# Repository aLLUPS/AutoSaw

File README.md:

# AutoSaw

This repository contains the information about ATMEGA 32A micro-controller based project - The Automated Abrasive Saw - 'AutoSaw'.
* It is a machine which cuts long metal box bars into smaller pieces automatically, after the user enter the input length and number of pieces required.
* This repository consists:
    1. 3dModel:- The 3d model of the machine. (.FCSTD file & .stl file)
    2. Animation:- The animation about the operation of the machine.
    3. AtmelProject:- micro-C codes to program the whole machine.
    4. PCB:- The Printed circuit board design, the wiring of Electronic/Electric components with PCB.

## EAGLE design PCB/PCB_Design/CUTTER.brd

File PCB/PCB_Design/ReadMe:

* This folder contains the eagle project and images of the pcb design
* You can open the .sch and .brd files using Audodesk EAGLE software.

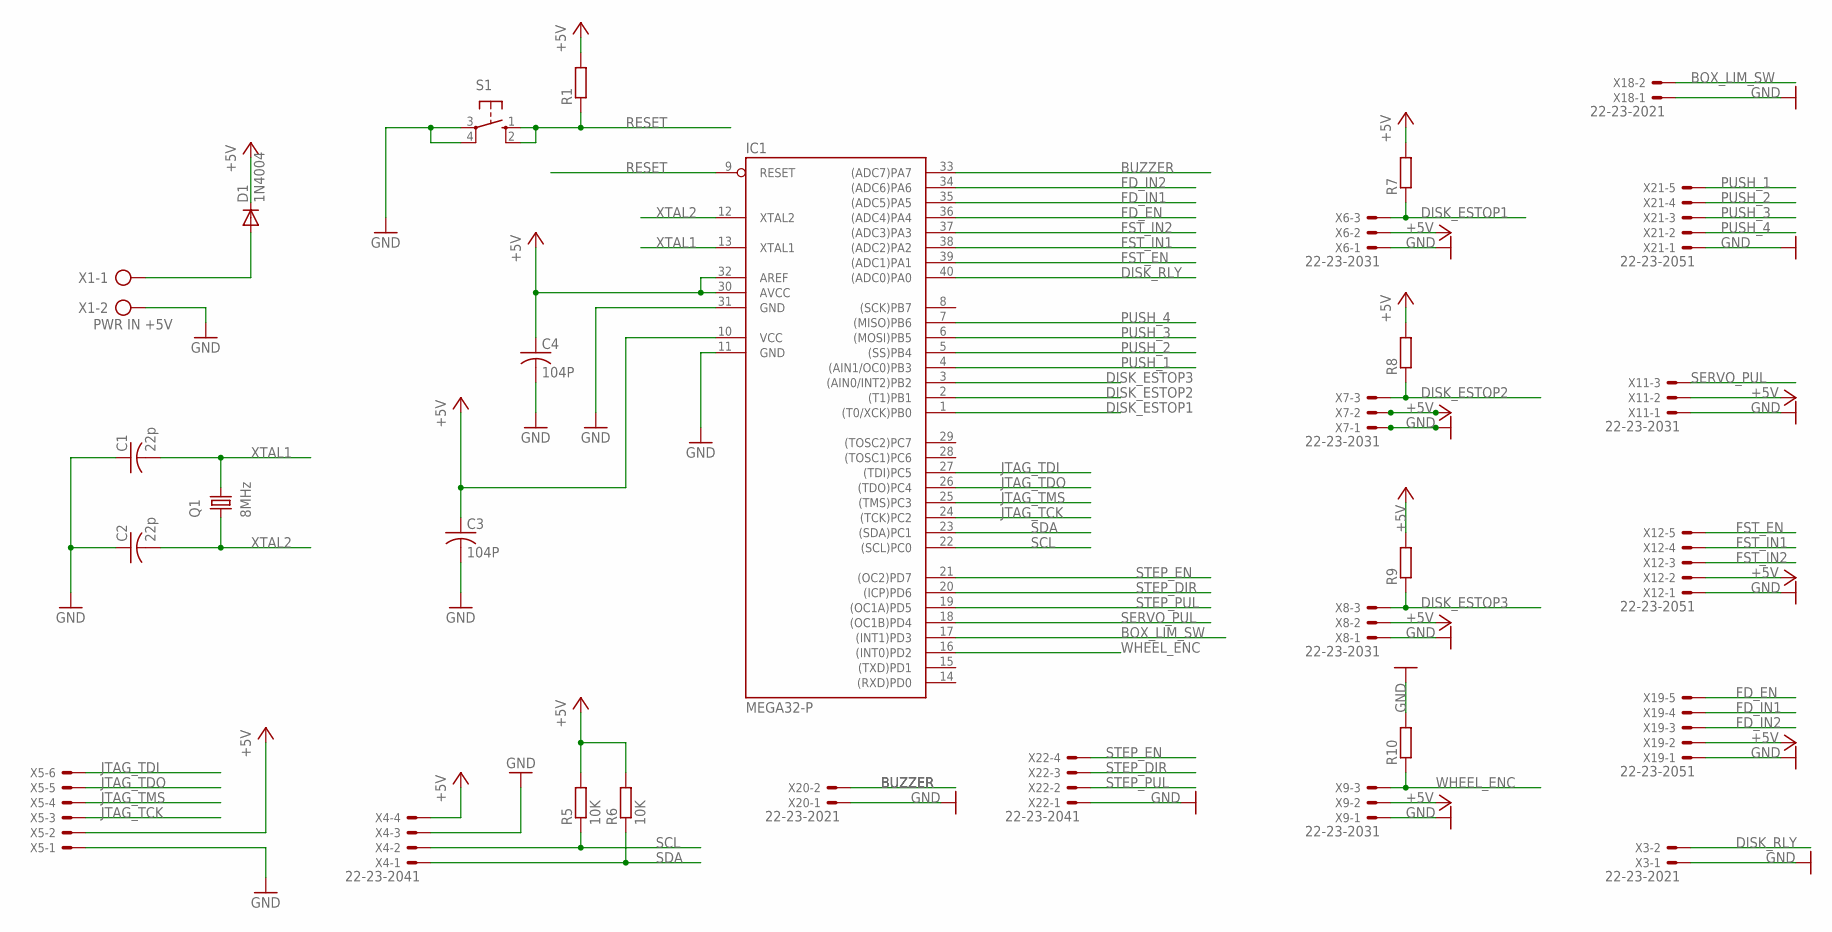
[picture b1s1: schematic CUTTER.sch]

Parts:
C1, C2: 22p; C025-025X050
C3, C4: 104P; C025-025X050
D1: 1N4004; DO41-10
IC1: MEGA32-P; DIL40
Q1: 8MHz; HC49/S
R1, R7, R8, R9, R10: R-EU_0207/10; 0207/10
R5, R6: 10K; 0207/10
S1: 10-XX; B3F-10XX
X1: PWR IN +5V; AK500/2
X3, X18, X20: 22-23-2021
X4, X22: 22-23-2041
X5: 22-23-2061
X6, X7, X8, X9, X11: 22-23-2031
X12, X19, X21: 22-23-2051

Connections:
+5V: C3.1, C4.1, D1.C, IC1.10 (VCC), IC1.30 (AVCC), IC1.32 (AREF), R1.2, R5.2, R6.2, R7.2, R8.2, R9.2, X4.4, X5.2, X6.2, X7.2, X8.2, X9.2, X11.2, X12.2, X19.2
BOX_LIM_SW: IC1.17 ((INT1)PD3), X18.2
BUZZER: IC1.33 ((ADC7)PA7), X20.2
DISK_ESTOP1: IC1.1 ((T0/XCK)PB0), R7.1, X6.3
DISK_ESTOP2: IC1.2 ((T1)PB1), R8.1, X7.3
DISK_ESTOP3: IC1.3 ((AIN0/INT2)PB2), R9.1, X8.3
DISK_RLY: IC1.40 ((ADC0)PA0), X3.2
FD_EN: IC1.36 ((ADC4)PA4), X19.5
FD_IN1: IC1.35 ((ADC5)PA5), X19.4
FD_IN2: IC1.34 ((ADC6)PA6), X19.3
FST_EN: IC1.39 ((ADC1)PA1), X12.5
FST_IN1: IC1.38 ((ADC2)PA2), X12.4
FST_IN2: IC1.37 ((ADC3)PA3), X12.3
GND: C1.1, C2.1, C3.2, C4.2, IC1.11 (GND), IC1.31 (GND), R10.2, S1.3, S1.4 (P1), X1.2, X3.1, X4.3, X5.1, X6.1, X7.1, X8.1, X9.1, X11.1, X12.1, X18.1, X19.1, X20.1, X21.1, X22.1
JTAG_TCK: IC1.24 ((TCK)PC2), X5.3
JTAG_TDI: IC1.27 ((TDI)PC5), X5.6
JTAG_TDO: IC1.26 ((TDO)PC4), X5.5
JTAG_TMS: IC1.25 ((TMS)PC3), X5.4
unnamed: D1.A, X1.1
PUSH_1: IC1.4 ((AIN1/OC0)PB3), X21.5
PUSH_2: IC1.5 ((SS)PB4), X21.4
PUSH_3: IC1.6 ((MOSI)PB5), X21.3
PUSH_4: IC1.7 ((MISO)PB6), X21.2
RESET: IC1.9 (RESET), R1.1, S1.1 (S), S1.2 (S1)
SCL: IC1.22 ((SCL)PC0), R5.1, X4.2
SDA: IC1.23 ((SDA)PC1), R6.1, X4.1
SERVO_PUL: IC1.18 ((OC1B)PD4), X11.3
STEP_DIR: IC1.20 ((ICP)PD6), X22.3
STEP_EN: IC1.21 ((OC2)PD7), X22.4
STEP_PUL: IC1.19 ((OC1A)PD5), X22.2
WHEEL_ENC: IC1.16 ((INT0)PD2), R10.1, X9.3
XTAL1: C1.2, IC1.13 (XTAL1), Q1.2
XTAL2: C2.2, IC1.12 (XTAL2), Q1.1

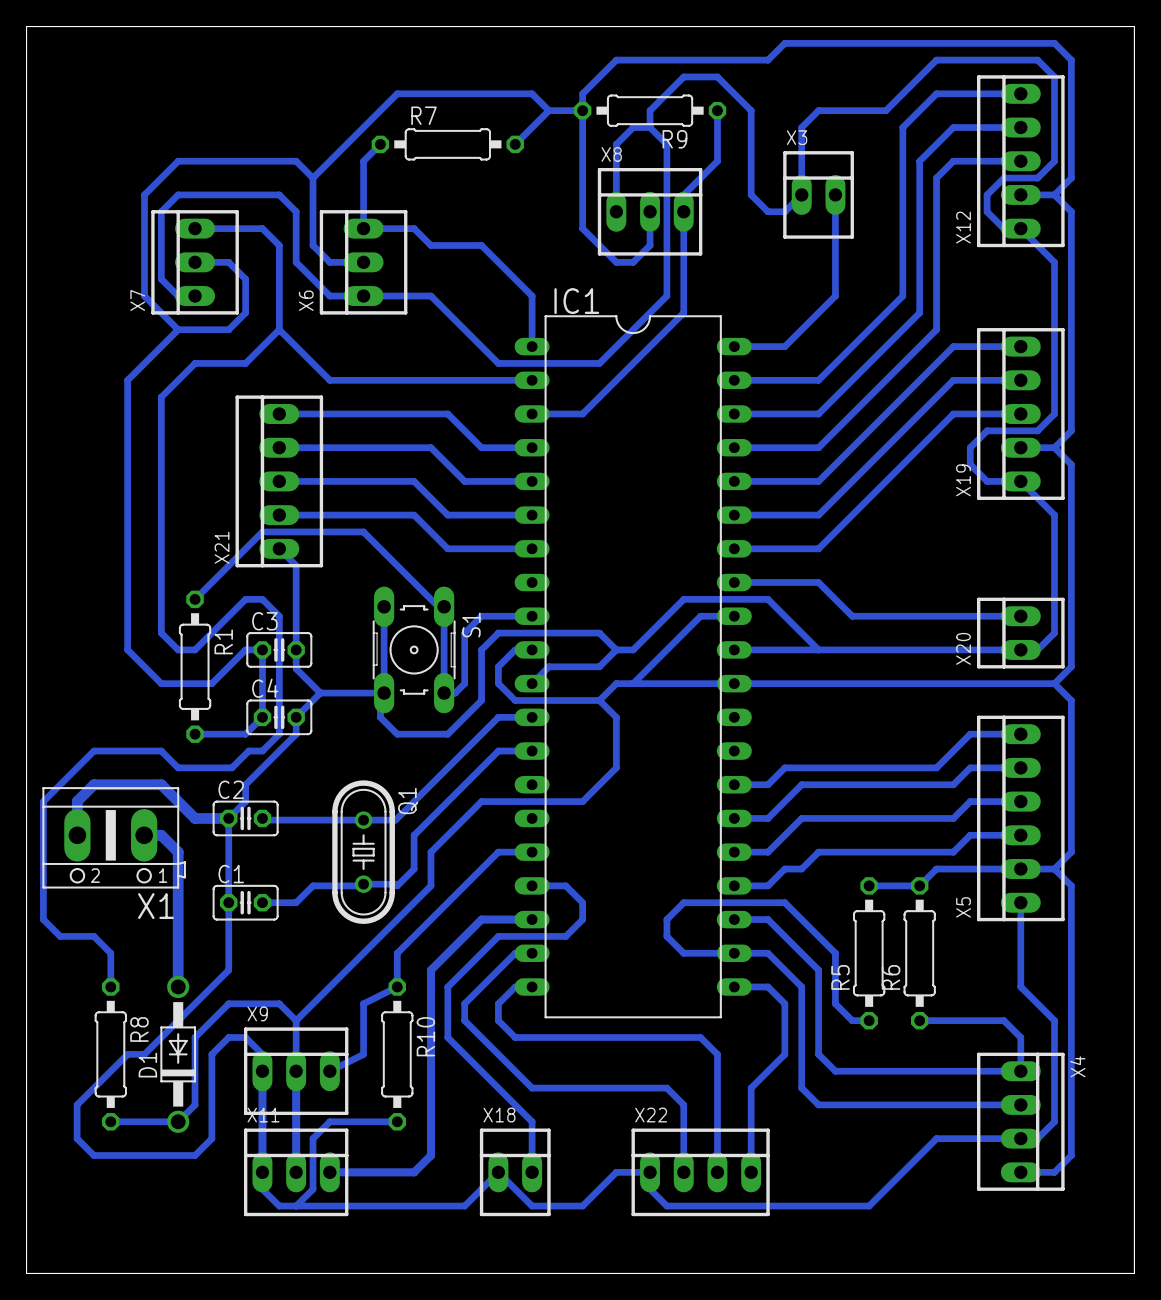
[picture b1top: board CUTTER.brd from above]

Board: 2 copper layers, 83.5 x 94.0 mm, 30 parts (0 on the bottom side), 33 nets.

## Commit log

2020-04-08 Create The main C code
2020-04-08 Create new folder
2020-04-11 add The3Dmodel.FCStd
2020-04-13 Create PCB_Design
2020-08-22 Set theme jekyll-theme-dinky
2020-08-22 Set theme jekyll-theme-slate
